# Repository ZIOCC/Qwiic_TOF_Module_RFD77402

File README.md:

# Qwiic TOF Module (RFD77402)

> This product can be available for purchase [here](https://www.smart-prototyping.com/Zio-TOF-Distance-Sensor-RFD77402.html).

#### Description

In the words of a team member, “kind of dope AF”, this Zio ToF Distance Sensor measures distance faster than the Flash can cover it. If you don’t believe us, you can ask him.

This little board features an RFD77402 time-of-flight rangefinding IC, measuring up to 2m in distance. The sensor uses a vertical-cavity surface-emitting laser (or VCSEL), and measures the time it takes for photons to make the round-trip to the laser’s target, and back to the built-in detector. The laser emitter is class 1, therefore safe for most all applications.

We’ve outfitted the board with mounting holes on wing tabs that can be snapped off to create an even smaller board if you don’t need them. Two Qwiic connectors occupy either side of the breakout board so you can quickly and easily daisy-chain it with other modules. It also includes a standard-pitch header for use with projects that aren’t Qwiic-based.

Apply this sensor in a wide-range of applications such as in robotics for obstacle detection and avoidance, 1D gesture recognition, hand detection, volume or height control, relative position of linear actuators, or for user proximity detection for IoT devices.

Check out this Brick Breaker game that we hacked together using a similar sensor.

#### Specification

* Light Source: VCSEL / 850 nm
* Field of Illumination: 29-degree @ 1/e2
* Field of View: 55-degree @ 1/e2
* Measurement Range: 100-2000mm
* Refresh Rate: 10Hz
* Precision: ±10%
* Laser Eye Safety: Class 1
* Current Consumption: 7-15mA
* IC: RFD77402
* I2C address: 0x4C
* Dimensions: 16.5x 26.3mm (with mounting bar). 26.3x10.5mm (without mounting bar)
* Weight: 1.2g

#### Links

* [RFD77402 Datasheet](https://www.smart-prototyping.com/image/data/NOA-RnD/101891%20TOF/RFD77402DatasheetRev1-8.pdf)
* [SparkFun RFD77402  Library](https://github.com/sparkfun/SparkFun_RFD77402_Arduino_Library)
* [Eagle files](https://github.com/ZIOCC/Qwiic_TOF_Module_RFD77402)

> ###### About Zio
> Zio is a new line of open sourced, compact, and grid layout boards, fully integrated for Arduino and Qwiic ecosystem. Designed ideally for wearables, robotics, small-space limitations or other on the go projects. Check out other awesome Zio products [here](https://www.smart-prototyping.com/Zio).

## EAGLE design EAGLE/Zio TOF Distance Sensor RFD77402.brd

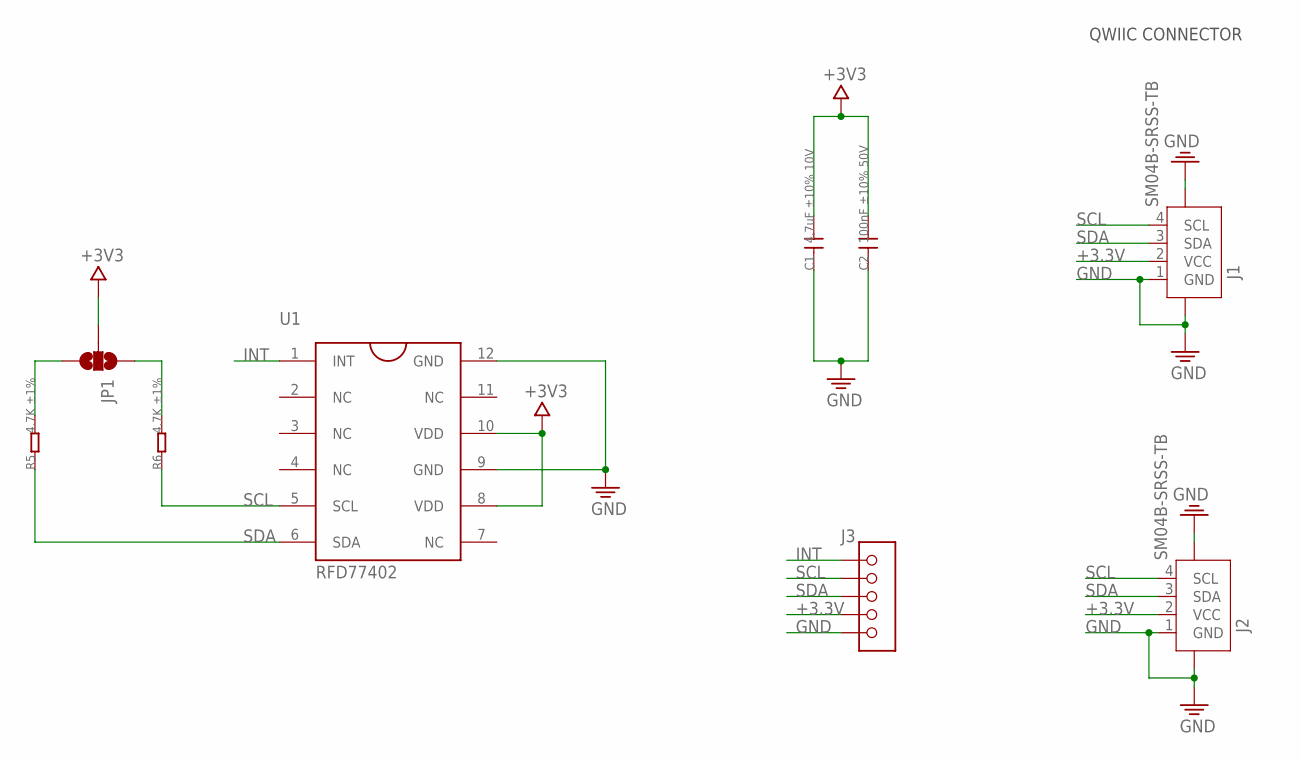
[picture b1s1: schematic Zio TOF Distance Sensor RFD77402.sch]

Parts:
C1: 4.7uF ±10% 10V; 0603
C2: 100nF ±10% 50V; 0603
J1, J2: SM04B-SRSS-TB; JST-SH-4P
J3: HEADER-5P-2.54; 5P-2.54
JP1: JUMPER-SMT_3_2-NC_PASTE_NOCREM; SMT-JUMPER_3_2-NC_PASTE_SILK_NOCREM
R5, R6: 4.7K ±1%; 0603
U1: RFD77402

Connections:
+3.3V: C1.2, C2.2, J1.2 (VCC), J2.2 (VCC), J3.4, JP1.2, U1.8 (VDD), U1.10 (VDD)
GND: C1.1, C2.1, J1.1 (GND), J1.NC1 (5), J1.NC2 (6), J2.1 (GND), J2.NC1 (5), J2.NC2 (6), J3.5, U1.9 (GND), U1.12 (GND)
INT: J3.1, U1.1 (INT)
unnamed: JP1.3, R5.2
unnamed: JP1.1, R6.2
SCL: J1.4 (SCL), J2.4 (SCL), J3.2, R6.1, U1.5 (SCL)
SDA: J1.3 (SDA), J2.3 (SDA), J3.3, R5.1, U1.6 (SDA)

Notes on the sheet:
QWIIC CONNECTOR

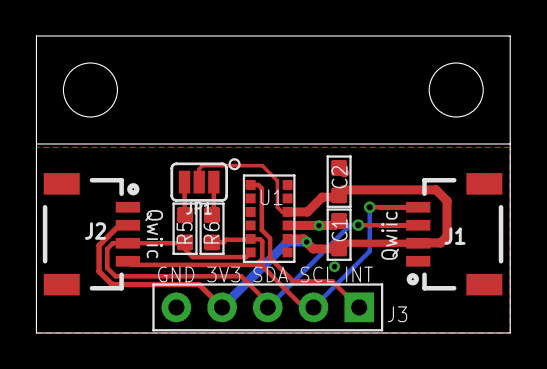
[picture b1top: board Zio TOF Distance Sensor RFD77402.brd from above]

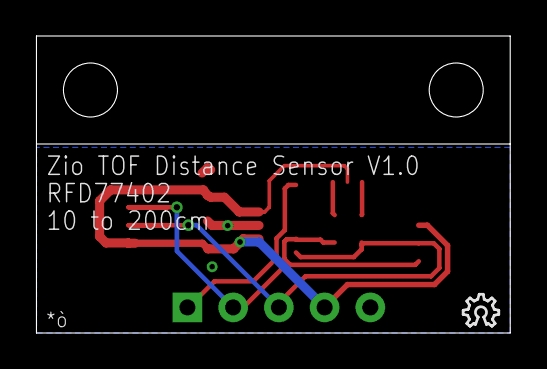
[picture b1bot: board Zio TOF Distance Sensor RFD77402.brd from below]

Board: 2 copper layers, 26.3 x 16.4 mm, 11 parts (2 on the bottom side), 7 nets.

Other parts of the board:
E$3: 6MM
LOGO1: LOGO-OSHW-6MILX0070-NT; OSHW_6X70_NOTEXT
